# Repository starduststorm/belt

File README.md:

belt move, triangle stay put. that's it. that's the concept.

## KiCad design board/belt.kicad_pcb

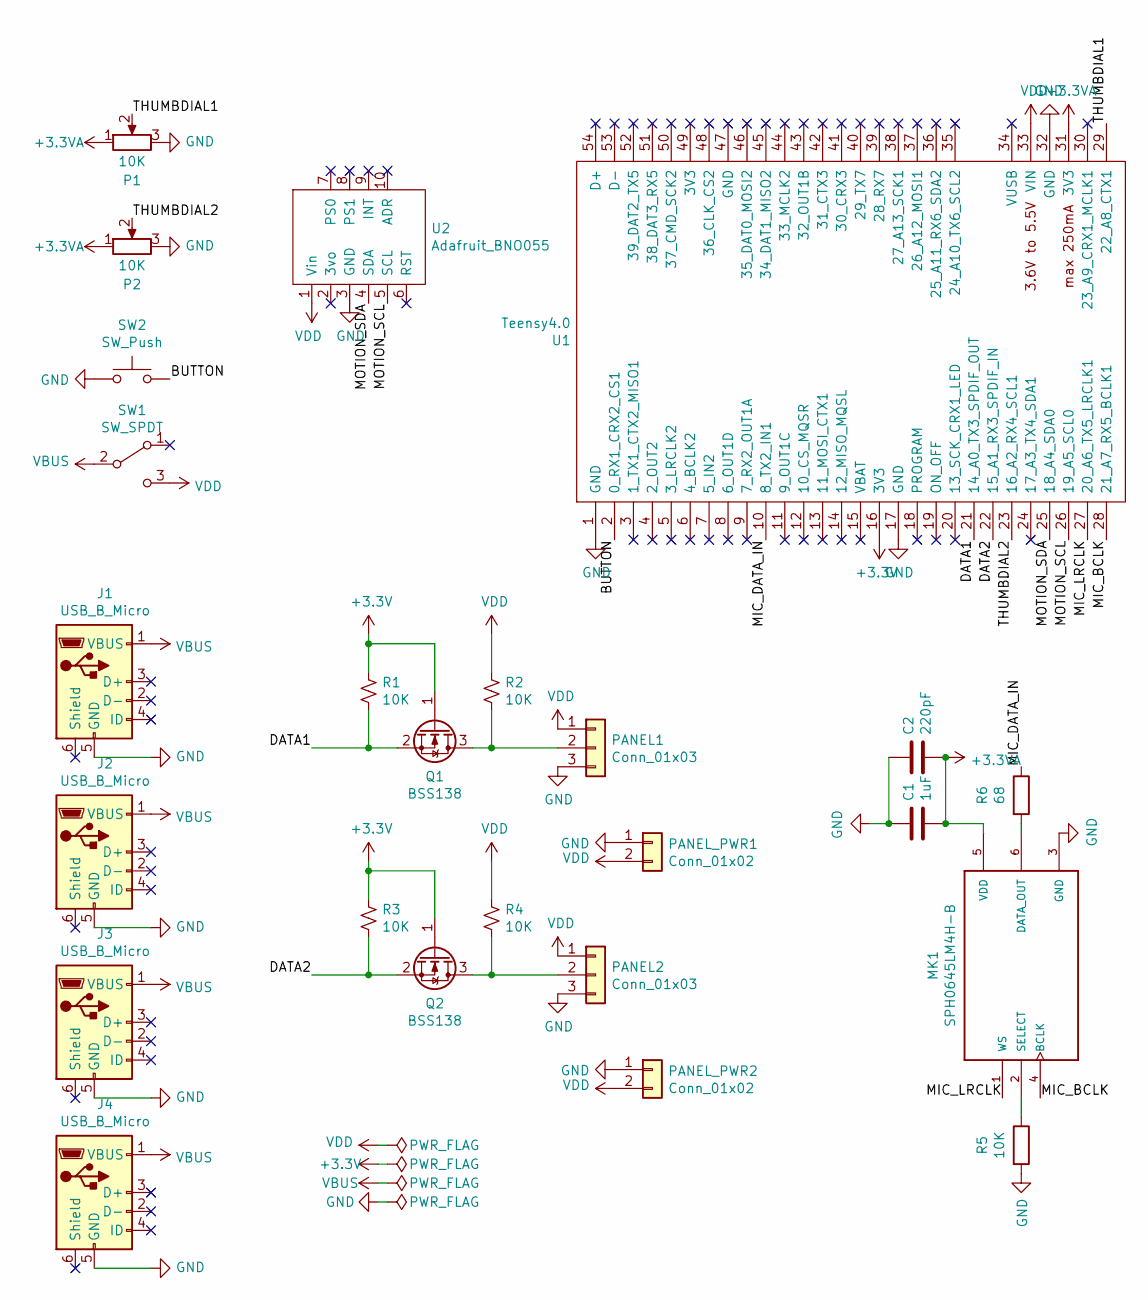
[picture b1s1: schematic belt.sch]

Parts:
C1: 1uF; C_0805_2012Metric
C2: 220pF; C_0805_2012Metric
J1, J2, J3, J4: USB_B_Micro; USB_Micro-B_Molex-105017-0001
MK1: SPH0645LM4H-B; MIC_SPH0645LM4H-B
P1, P2: 10K; PDB12-H
PANEL1, PANEL2: Conn_01x03; Pad_SMD_01x03
PANEL_PWR1, PANEL_PWR2: Conn_01x02; Pad_SMD_01x02
Q1, Q2: BSS138; SOT-23
R1, R2, R3, R4, R5: 10K; R_0603_1608Metric
R6: 68; R_0805_2012Metric
SW1: SW_SPDT; Button_Switch_SPDT_GH36P010001
SW2: SW_Push; SW_PUSH_6mm_H5mm
U1: Teensy4.0; Teensy40
U2: Adafruit_BNO055

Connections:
+3.3VA: C1.2, C2.2, MK1.5 (VDD), P1.1, P2.1, U1.31 (3V3)
+3V3: Q1.1 (G), Q2.1 (G), R1.1, R3.1, U1.16 (3V3)
/BUTTON: SW2.2, U1.2 (0_RX1_CRX2_CS1)
/DATA1: Q1.2 (S), R1.2, U1.21 (14_A0_TX3_SPDIF_OUT)
/DATA2: Q2.2 (S), R3.2, U1.22 (15_A1_RX3_SPDIF_IN)
/MIC_BCLK: MK1.4 (BCLK), U1.28 (21_A7_RX5_BCLK1)
/MIC_DATA_IN: R6.1, U1.10 (8_TX2_IN1)
/MIC_LRCLK: MK1.1 (WS), U1.27 (20_A6_TX5_LRCLK1)
/MOTION_SCL: U1.26 (19_A5_SCL0), U2.5 (SCL)
/MOTION_SDA: U1.25 (18_A4_SDA0), U2.4 (SDA)
/THUMBDIAL1: P1.2, U1.29 (22_A8_CTX1)
/THUMBDIAL2: P2.2, U1.23 (16_A2_RX4_SCL1)
GND: C1.1, C2.1, J1.5 (GND), J2.5 (GND), J3.5 (GND), J4.5 (GND), MK1.3 (GND), P1.3, P2.3, PANEL1.3, PANEL2.3, PANEL_PWR1.1, PANEL_PWR2.1, R5.2, SW2.1, U1.1 (GND), U1.17 (GND), U1.32 (GND), U2.3 (GND)
unnamed: MK1.2 (SELECT), R5.1
unnamed: MK1.6 (DATA_OUT), R6.2
unnamed: PANEL1.2, Q1.3 (D), R2.2
unnamed: PANEL2.2, Q2.3 (D), R4.2
VBUS: J1.1 (VBUS), J2.1 (VBUS), J3.1 (VBUS), J4.1 (VBUS), SW1.2 (B)
VDD: PANEL1.1, PANEL2.1, PANEL_PWR1.2, PANEL_PWR2.2, R2.1, R4.1, SW1.3 (C), U1.33 (VIN), U2.1 (Vin)

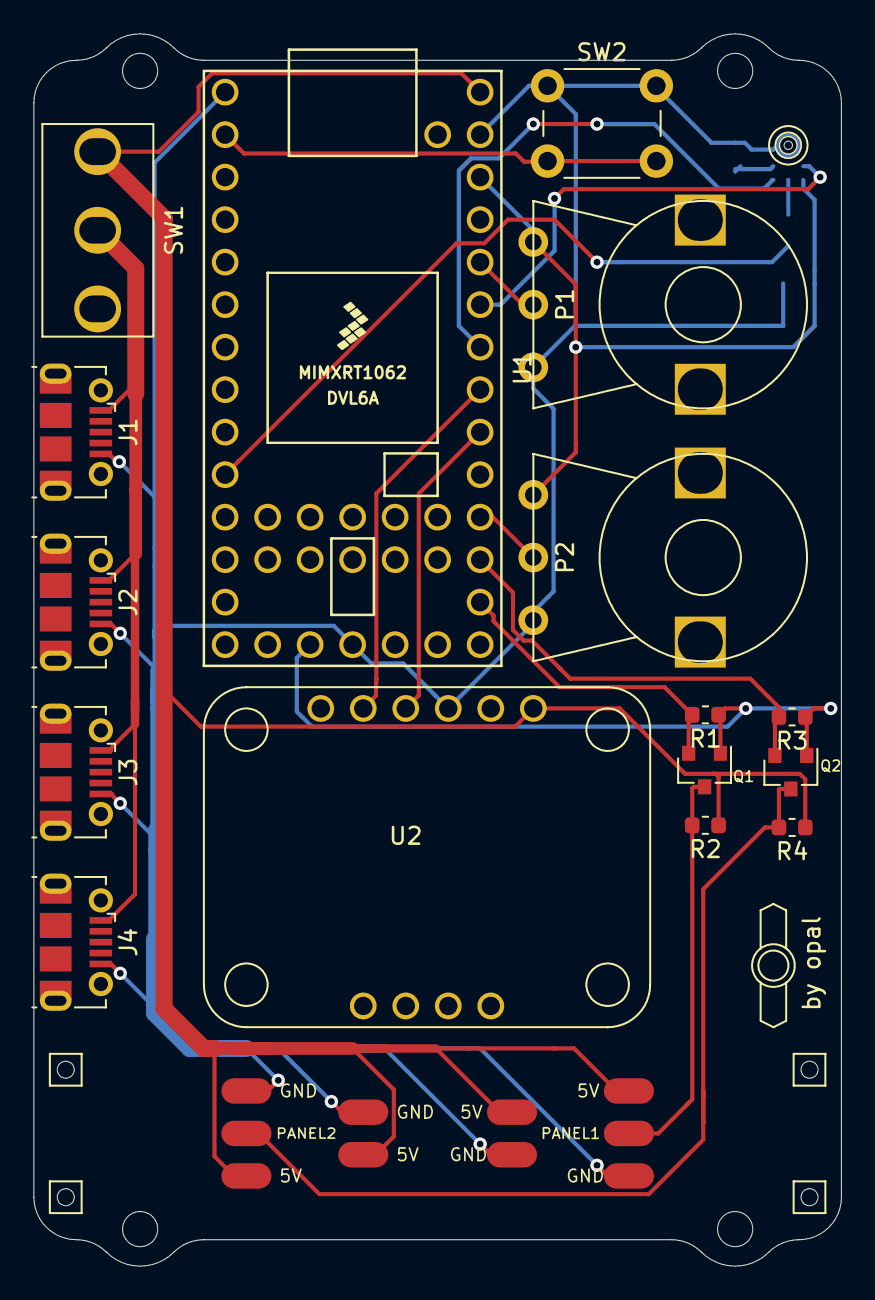
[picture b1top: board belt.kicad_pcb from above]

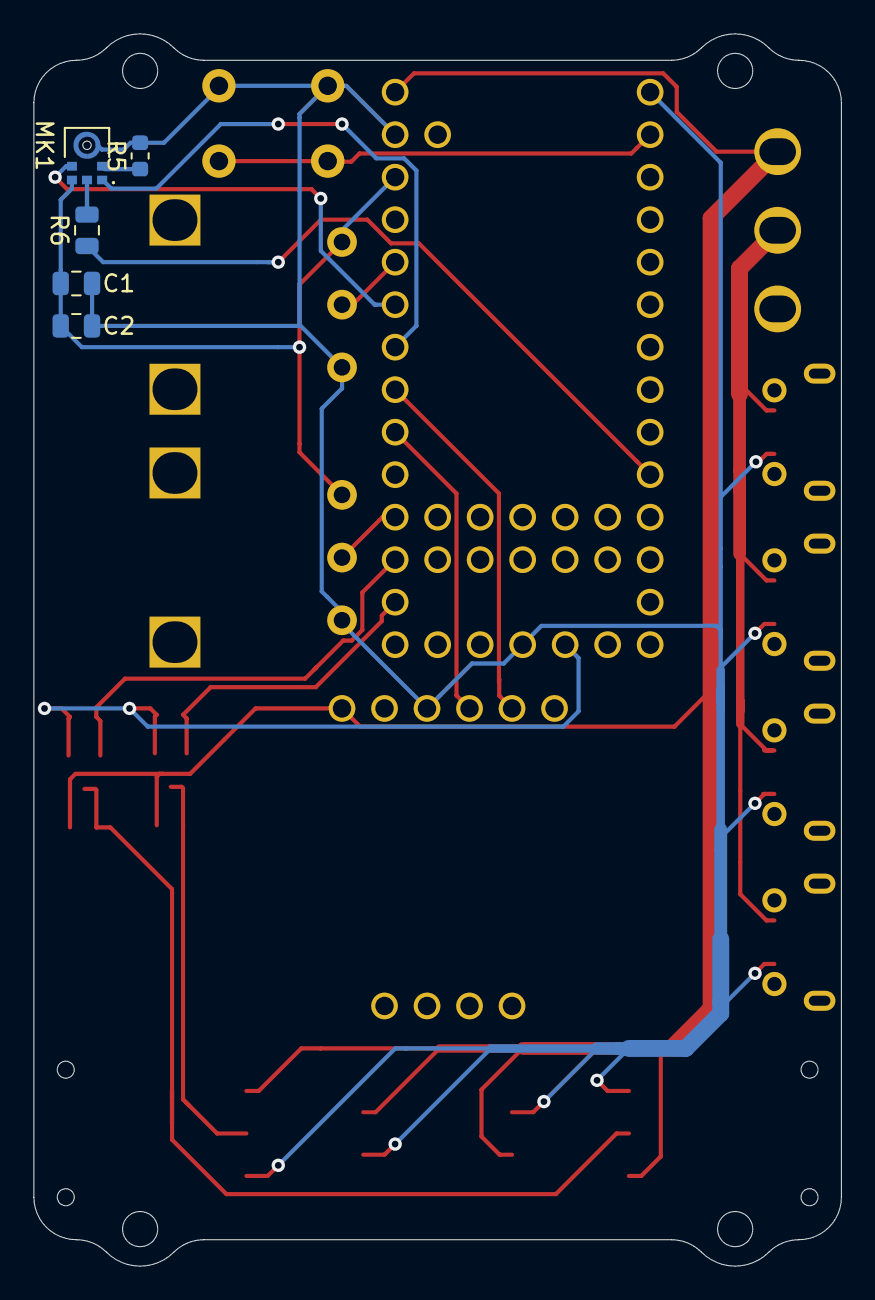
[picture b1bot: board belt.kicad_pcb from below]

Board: 2 copper layers, 48.3 x 73.6 mm, 25 parts (5 on the bottom side), 19 nets.

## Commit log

2020-01-29 initial commit of work-in-progress LED belt
2020-01-30 first pass at pcb layout; also start looking into adding an NPN switch so that LED current doesn't have to travel through the rest of the board (concerns about wire thickness, heat, etc.)
2020-01-31 alternate layout with thick wires and switch on top to avoid needing a transistor to switch power nearby (would likely need a large transistor with a heatsink to manage the current)
2020-01-31 shuffle things around some more
2020-01-31 polish board edges; add mounting points
2020-02-01 move pot and button ports to be nearer by on teensy
2020-02-06 mostly done with next board iteration, except for new microphone; use new microphone in software to draw a rainbow fft that is super fun to play with
2020-02-08 checkpoint for 3rd board layout with veritcal structure, two pots, and digital mic
2020-02-09 new placement for led pads plus a strategy for securing them; tweaks; nearing final design
2020-02-09 narrow board width slightly and center led ports on the bottom
2020-02-09 digikey was out of the DPDT switch I was going to use, so replace with a smaller (better?) one; shrink board vertically slightly in response
2020-02-09 switch 10K resistors to 0603 package (being ambitious and buying in bulk); fix layout for new package
2020-02-09 fix schematic symbol which was using old POT symbol
2020-02-09 scoot pots apart to sorta be able to fit plastic tops
2020-02-09 fix slightly-off board outline cuts
2020-02-10 sign it
2020-02-10 flip entire board outline vertically which somehow fixed OSHPark thinking the outline wasn't contiguous
2020-02-15 factor AudioManager out of Pattern logic so multiple patterns can subscribe to audio data
2020-02-16 factor motion out into a non-pattern manager class; add a pattern based on Adafruit's PixelDust; disable sound processing since it sometimes prevents the teensy from initializing (memory related?)
2020-02-16 tweaks
2020-02-16 add missing MotionManager file
2020-02-17 start-up enhancements
2020-02-18 add in some rudimentary drawing helpers to encapsulate "blending" and shape drawing
2020-02-19 allow DrawingContext to be used in Pattern.update instead of directly accessing the CRGBArray; first pass on a pattern that reacts to rotational motion
2020-02-20 fiddle around with the idea of counter-moving lines
2020-02-25 play with oscillators; first test on assembled board
2020-02-25 do palette blends on fairy dust
2020-02-25 sound pattern should draw on every frame even if there is no fft data available; clean up a bit
2020-02-25 add a workaround for the unreliability of audio processing (just initialize motion first); get idle pattern rotation working with current patternset
2020-02-26 factor auto palette rotation into a type for patterns to opt-in to and adopt it from the Sound pattern; templatize PaletteManager and PaletteRotation to optionally support CRGBPalette256
2020-02-26 remove raver plaid
2020-02-26 adopt PaletteRotation in Bars, fix a couple bugs in PaletteRotation
2020-02-26 adopt PaletteRotation in PixelDust
2020-02-26 add controls.h to handle pots and button
2020-02-26 filtr out very dark colors when choosing non-black palette colors; add idea comments
2020-02-26 tweaks & fixes
2020-02-26 add a timeout to wait-for-serial and indicate the issue on panel
2020-02-26 belt -> src
2020-02-27 start porting project to PlatformIO; Audio still broken
2020-02-27 lint
2020-02-27 found the right lib for fft linking
2020-02-27 fix an issue with PixelDust starting and stopping multiple times
2020-02-27 apparently randomizing the pixels is a one-time thing too
2020-02-28 add janky antialiasing to line drawing; use it to add smooth motion responsiveness to Bars
2020-03-07 add PixelDust as PlatformIO dependency
2020-03-14 fix earlyDimming
2020-03-14 palettize Oscillators; tweaks to color handling and fadedowns, handling low light
2020-03-14 introduce FFTProcessing interface which allows patterns to subscribe to FFT data with a specific number of bins; use this new interface to give Oscillators an audio+motion treatment
2020-03-14 changes for first belt-mounted test
2020-03-14 Generalize HardwareControls class to support multiple potentiometers, polish it up for future hardware platforms
2020-03-14 smooth out potentiometer jitter for the brightness dial
2020-03-14 tweak fft-bin-size determination to prevent the first bin from being too small (1/512) the total fft bands) when there are ony a few (5) total bins
2020-03-15 stable checkpoint for patternmanager
2020-03-15 add missing patternmanager file
2020-03-15 cut out lazyStop and stopCompleted; remove "subPattern"s, clean up and simplify Pattern class; UNTESTED
2020-03-15 move lsb_noise to util.h; remove 'remap' that had a replacement in FastLED
2020-03-15 gitignore tweak for ProjectIO
2020-03-17 fix issue with test pattern not being 'start'ed
2020-03-17 add PatternManager to handle pattern lifecyle; cut out lazyStop and stopCompleted; remove "subPattern"s
2020-03-17 Rough auto-gain for AudioManager
2020-03-21 shift palette phase for oscillators to center the palette
2020-03-22 port Droplets to 2D - it's quite frenetic right now but looks cool. it should react to motion and/or sound and probably move slower too
2020-03-22 operate Droplets with a floating-point pixel buffer to give it better fidelity; step towards DrawingContext-owned pixel buffers
2020-03-27 fix an issue where randomness could very rarely cause an assertion failure
2020-05-15 Update Droplets to respond to audio, contains additional adaptive gain; looks pretty great
2020-05-17 Reduce stack-copying of large palette objects; port max-color-jump palette selector from strand lights
2021-07-07 move power switch footprint in a project-specific library and make it a bit more detailed
2021-07-08 first draft of a protective case for the belt pcb; a test print yielded tolerances that are too tight in multiple places so it neesd a second draft
2021-07-09 case v2 print looks good & fits!
2021-08-14 lib symbol tweaks
2021-08-14 don't make the the test idle pattern at launch time
2021-08-14 backport logging changes from evm
2021-08-14 rotate Sound spectrum pattern with orientation
2021-08-17 modff can't take NULL for its out ptr and somehow this *wasn't* crashing before now?
2021-08-18 smoothly rotate Droplets & Sound patterns to track reverse rotation motion
2021-08-18 move pixel buffer ownership into the drawing context
2021-08-19 tweak pixeldust motion to track sideways & twirl motion in more interesting ways; add a hack to avoid pixels getting stuck near the back (due to belt neutal position)
2021-08-19 wire second analog dial to manual audio gain management
2021-08-19 Sound pattern -> SpectrumAnalyzer
2021-08-19 customary 3am changes prior to the belt's debut event: overhaul 'Motion' pattern to draw bendy arrows in the direction of spin, looks great; reorder patterns; enable previousPattern on double-press; 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
2021-08-20 add a working compass mode at the last minute
2021-11-02 move several belt footprints into local belt footprint library; fix footprints for power switch and BNO055 which had through-holes that were too small
2021-11-11 tweak controller button on case for duability since the first one broke after some use
2021-12-13 Add new "mode" of MotionBlobs SpikeSpin, old now is now ArrowSpin; maybe in the future they can be same again, i.e. switch triggered by a jump or slow fade or something; fix issue where motionmanager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
2021-12-13 backport PaletteRotation updates from evm
2021-12-13 add next-level paletting to ArrowSpin it looks so good
2021-12-14 fix fft levels logging
2021-12-14 attempt to make case button more durable; tolerance tweaks
2021-12-18 gain tweaks - very loud sounds would scale back Droplets gain too quickly, leaving the panel off for a sec while the gain slowly came back
2021-12-18 add a janky "activity classifier" that can detect a jump (or a strong bounce) and use it to change something benign but fun for now
2021-12-31 jump tweaks to lower sensitivity, add logging
2022-01-01 add a skeleton for automatic mode switching based on motion data; motion data captured continuously into stats lib; "high" motion variance triggers switch to PixelDust if auto is enabled
2022-03-03 improve automatic pattern switching to crossfade to and from the high motion pattern based on sustained vertical motion variance
2022-03-03 fix the pattern tester
2022-03-03 replace janky line drawing with a ported Wu's algorithm for proper antialiased drawing
2022-03-08 results of fiddling around with triangles & motion a little bit
2022-03-08 remove pio stubs
2022-03-08 fix manually changing patterns during the "automatic" mode after it's switched to the high energy mode. "automatic mode" should be an enable-only feature that gets disabled when you set it manually.
2022-03-09 little refactor for auto mode; add brightness 'animations' that should come in useful later
2022-03-09 improvements to composition state management
2022-03-10 sweeping changes: add a twirl overlay in automatic mode that crossfades a random twirl pattern during twirls; export pattern flags statically so I can do things like pick a pattern that does twirl th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
2022-03-10 fix a build issue with one of the test flags; also add a FIXME for a new issue
2022-03-10 spice up the automatic mode animation and make it always enable, not toggle. change pattern to disable it.
2022-03-10 fade the active pattern back in after the auto-welcome using the at-launch fade in; silly but effective
2022-03-10 tune the twirl fadeup a little
2022-03-10 fix line drawing for Bars pattern
2022-03-10 tune the pixeldust z-correction to prevent pixels getting stuck on one side or the other during dancing
2022-03-10 shift Oscillators over by one fft bucket since the lowest bucket tends to be omitted or less interesting; also make it twirl
2022-03-11 factor out a WrappedBufferPattern to support full-arc drawing e.g. Compass; factor out some constants and belt-sizing parameters into config.h
2022-03-15 consolidate & cache calls into adafruit BNO and limit to once-per-frame-per-type; fix repeated calls to twirlVelocity improperly updating the accumulator; typical framerate unimproved, but automatic 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
2022-03-18 compass tweak
2022-06-10 more attempts to make the case button more durable
2022-06-28 trianglespin visual tweak
2022-06-28 compass should keep showing directions if we lose calibration for a short time
2022-06-29 tweaks to pixeldust physics to better capture rotational jerk
2022-07-05 add a detailed project description resulting from in-field testing
2022-10-30 i think zcorrect was over correcting; also some spikespin changes sitting in wc
